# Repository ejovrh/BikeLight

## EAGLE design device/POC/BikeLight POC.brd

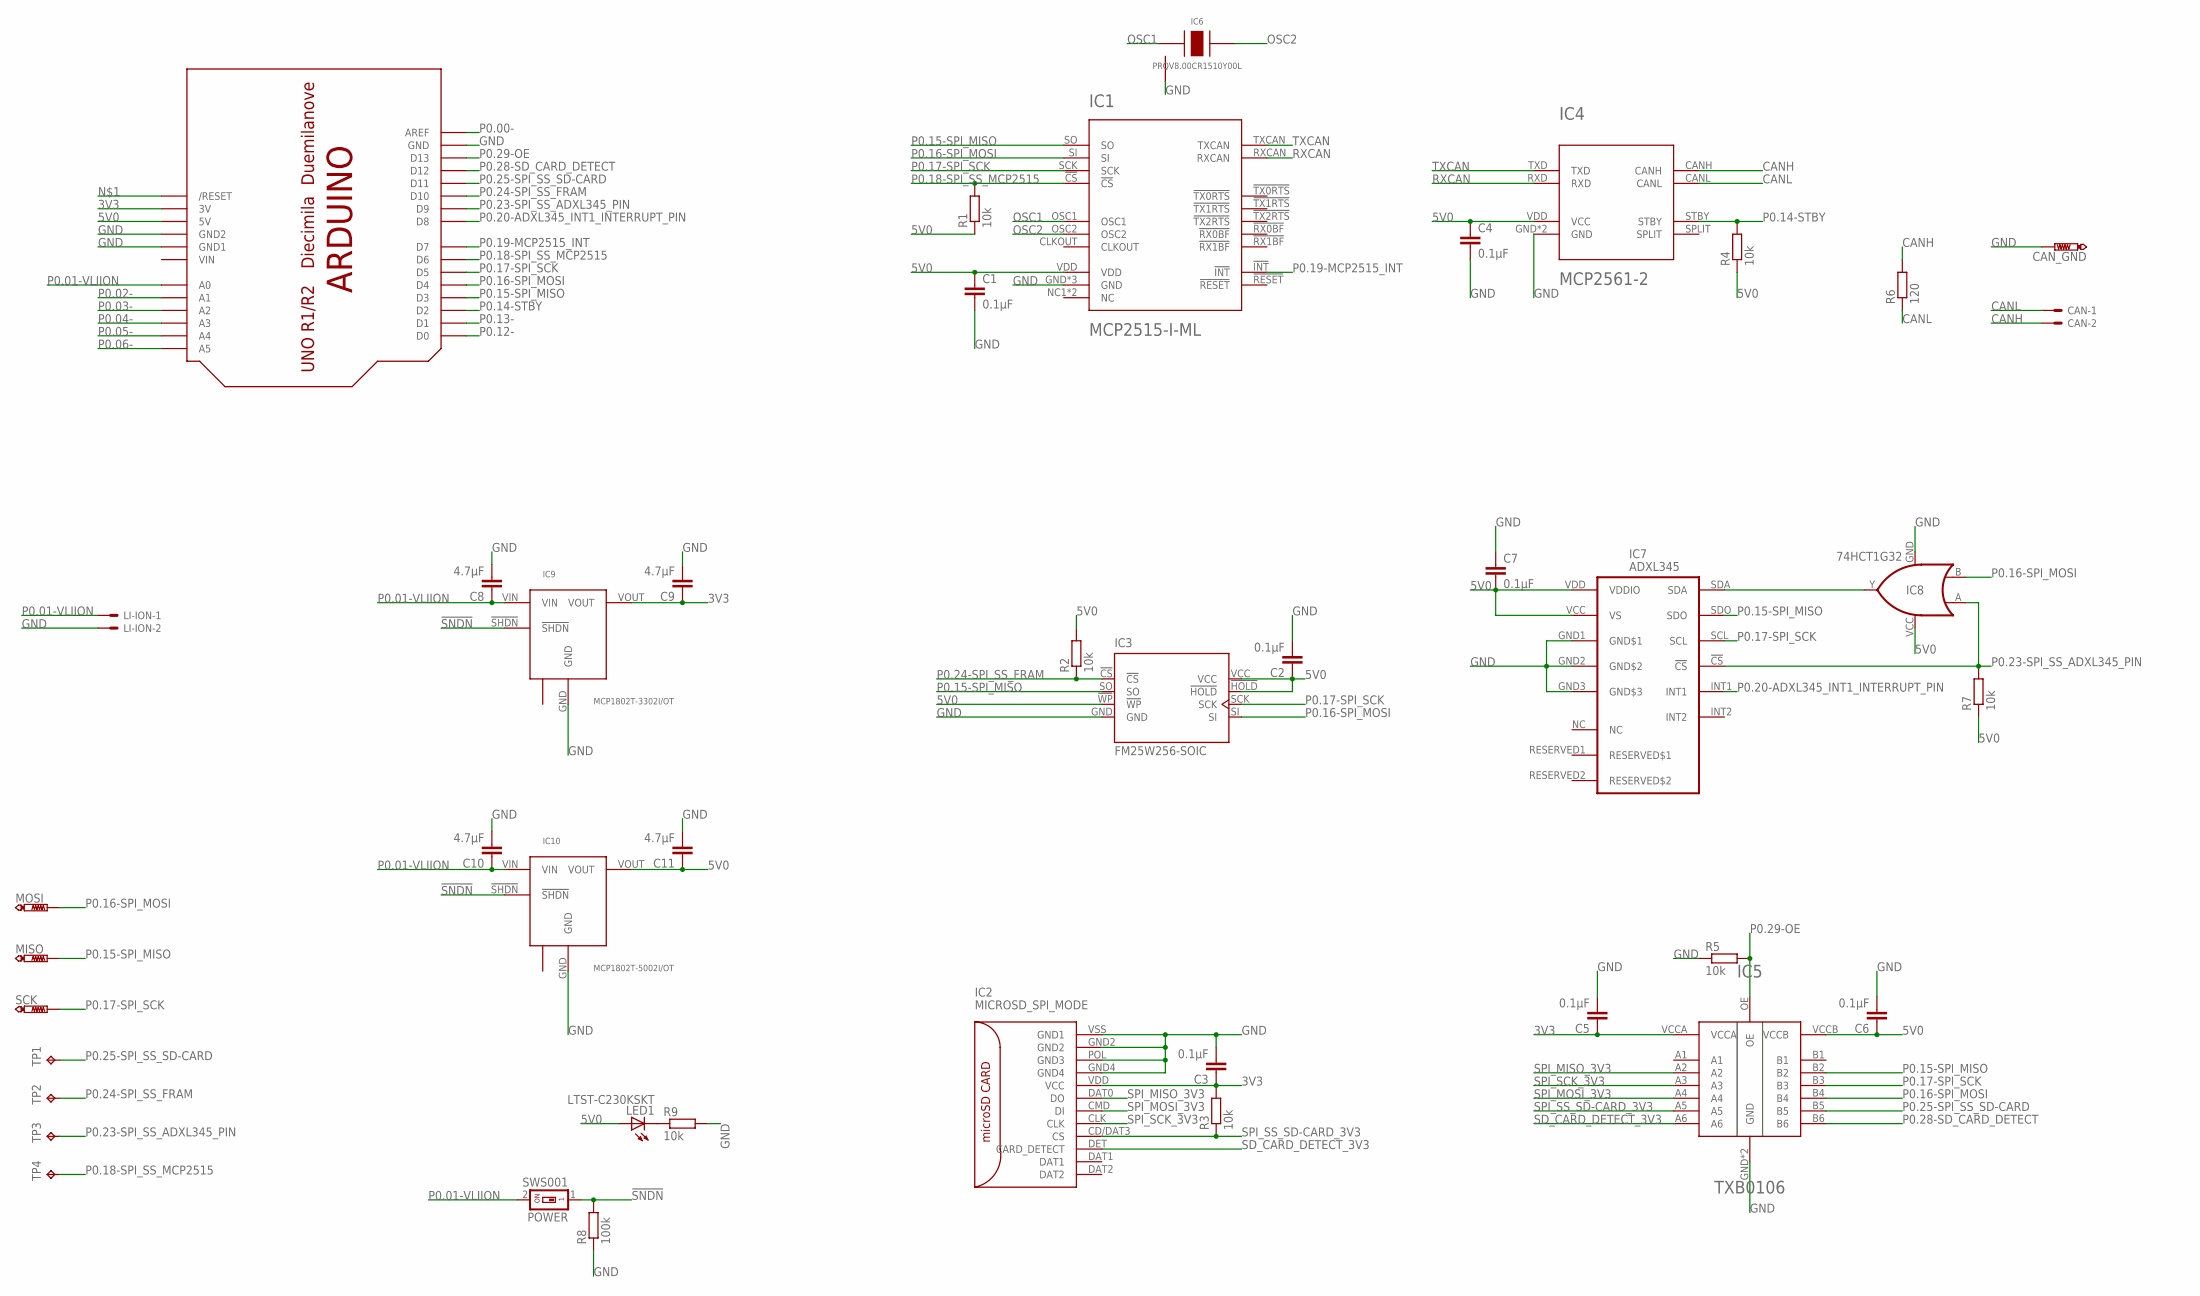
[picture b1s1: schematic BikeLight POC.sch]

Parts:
BRD1: BikeLight POC; ARDUINO
C1, C2, C3, C4, C5, C6, C7: 0.1μF; C0805
C8, C9, C10, C11: 4.7μF; C0805
CAN: 22-23-2021
CAN_GND: PTR1PAD1-13Y; P1-13Y
IC1: MCP2515-I-ML; QFN20
IC2: MICROSD_SPI_MODE; MICRO_SD_CONNECTOR
IC3: FM25W256-SOIC; SOIC08
IC4: MCP2561-2; DFN10
IC5: TXB0106; VQFN16
IC6: PRQV8.00CR1510Y00L; SMT
IC7: ADXL345; LGA14
IC8: 74HCT1G32; SOT353/5
IC9: MCP1802T-3302I/OT; SOT23-5
IC10: MCP1802T-5002I/OT; SOT23-5
LED1: LTST-C230KSKT; CHIPLED_1206
LI-ION: 22-23-2021
MISO: PTR1PAD1-13Y; P1-13Y
MOSI: PTR1PAD1-13Y; P1-13Y
POWER: SWS001; SMS-001
R1, R2, R3, R4, R5, R7, R9: 10k; R0805
R6: 120; R0805
R8: 100k; R0805
SCK: PTR1PAD1-13Y; P1-13Y
TP1, TP2, TP3, TP4: TPPAD1-13; P1-13

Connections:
3V3: BRD1.3V, C3.1, C5.1, C9.1, IC2.VDD (VCC), IC5.VCCA, IC9.VOUT, R3.2
5V0: BRD1.5V, C1.1, C2.1, C4.1, C6.1, C7.2, C11.1, IC1.VDD, IC3.!HOLD!, IC3.!WP!, IC3.VCC, IC4.VDD (VCC), IC5.VCCB, IC7.VCC (VS), IC7.VDD (VDDIO), IC8.VCC, IC10.VOUT, LED1.A, R1.1, R2.2, R4.1, R7.1
!SNDN!: IC9.!SHDN!, IC10.!SHDN!, POWER.1, R8.2
CANH: CAN.2, IC4.CANH, R6.2
CANL: CAN.1, IC4.CANL, R6.1
GND: BRD1.GND, BRD1.GND1, BRD1.GND2, C1.2, C2.2, C3.2, C4.2, C5.2, C6.2, C7.1, C8.2, C9.2, C10.2, C11.2, CAN_GND.TP, IC1.GND, IC1.GND1 (GND), IC1.GND6 (GND), IC2.GND2, IC2.GND4, IC2.POL (GND3), IC2.VSS (GND1), IC3.GND, IC4.GND, IC4.VSS (GND), IC5.GND, IC5.GND1 (GND), IC6.GND, IC7.GND1 (GND$1), IC7.GND2 (GND$2), IC7.GND3 (GND$3), IC8.GND, IC9.GND, IC10.GND, LI-ION.2, R5.1, R8.1, R9.2
unnamed: LED1.C, R9.1
OSC1: IC1.OSC1, IC6.XTAL1
OSC2: IC1.OSC2, IC6.XTAL2
P0.00-: BRD1.AREF
P0.01-VLIION: BRD1.A0, C8.1, C10.1, IC9.VIN, IC10.VIN, LI-ION.1, POWER.2
P0.02-: BRD1.A1
P0.03-: BRD1.A2
P0.04-: BRD1.A3
P0.05-: BRD1.A4
P0.06-: BRD1.A5
P0.12-: BRD1.D0
P0.13-: BRD1.D1
P0.14-STBY: BRD1.D2, IC4.STBY, R4.2
P0.15-SPI_MISO: BRD1.D3, IC1.SO, IC3.SO, IC5.B2, IC7.SDO, MISO.TP
P0.16-SPI_MOSI: BRD1.D4, IC1.SI, IC3.SI, IC5.B4, IC8.B, MOSI.TP
P0.17-SPI_SCK: BRD1.D5, IC1.SCK, IC3.SCK, IC5.B3, IC7.SCL, SCK.TP
P0.18-SPI_SS_MCP2515: BRD1.D6, IC1.!CS!, R1.2, TP4.TP
P0.19-MCP2515_INT: BRD1.D7, IC1.!INT!
P0.20-ADXL345_INT1_INTERRUPT_PIN: BRD1.D8, IC7.INT1
P0.23-SPI_SS_ADXL345_PIN: BRD1.D9, IC7.!CS!, IC8.A, R7.2, TP3.TP
P0.24-SPI_SS_FRAM: BRD1.D10, IC3.!CS!, R2.1, TP2.TP
P0.25-SPI_SS_SD-CARD: BRD1.D11, IC5.B5, TP1.TP
P0.28-SD_CARD_DETECT: BRD1.D12, IC5.B6
P0.29-OE: BRD1.D13, IC5.OE, R5.2
RXCAN: IC1.RXCAN, IC4.RXD
SDA: IC7.SDA, IC8.Y
SD_CARD_DETECT_3V3: IC2.DET (CARD_DETECT), IC5.A6
SPI_MISO_3V3: IC2.DAT0 (DO), IC5.A2
SPI_MOSI_3V3: IC2.CMD (DI), IC5.A4
SPI_SCK_3V3: IC2.CLK, IC5.A3
SPI_SS_SD-CARD_3V3: IC2.CD/DAT3 (CS), IC5.A5, R3.1
TXCAN: IC1.TXCAN, IC4.TXD
VIN: BRD1.VIN

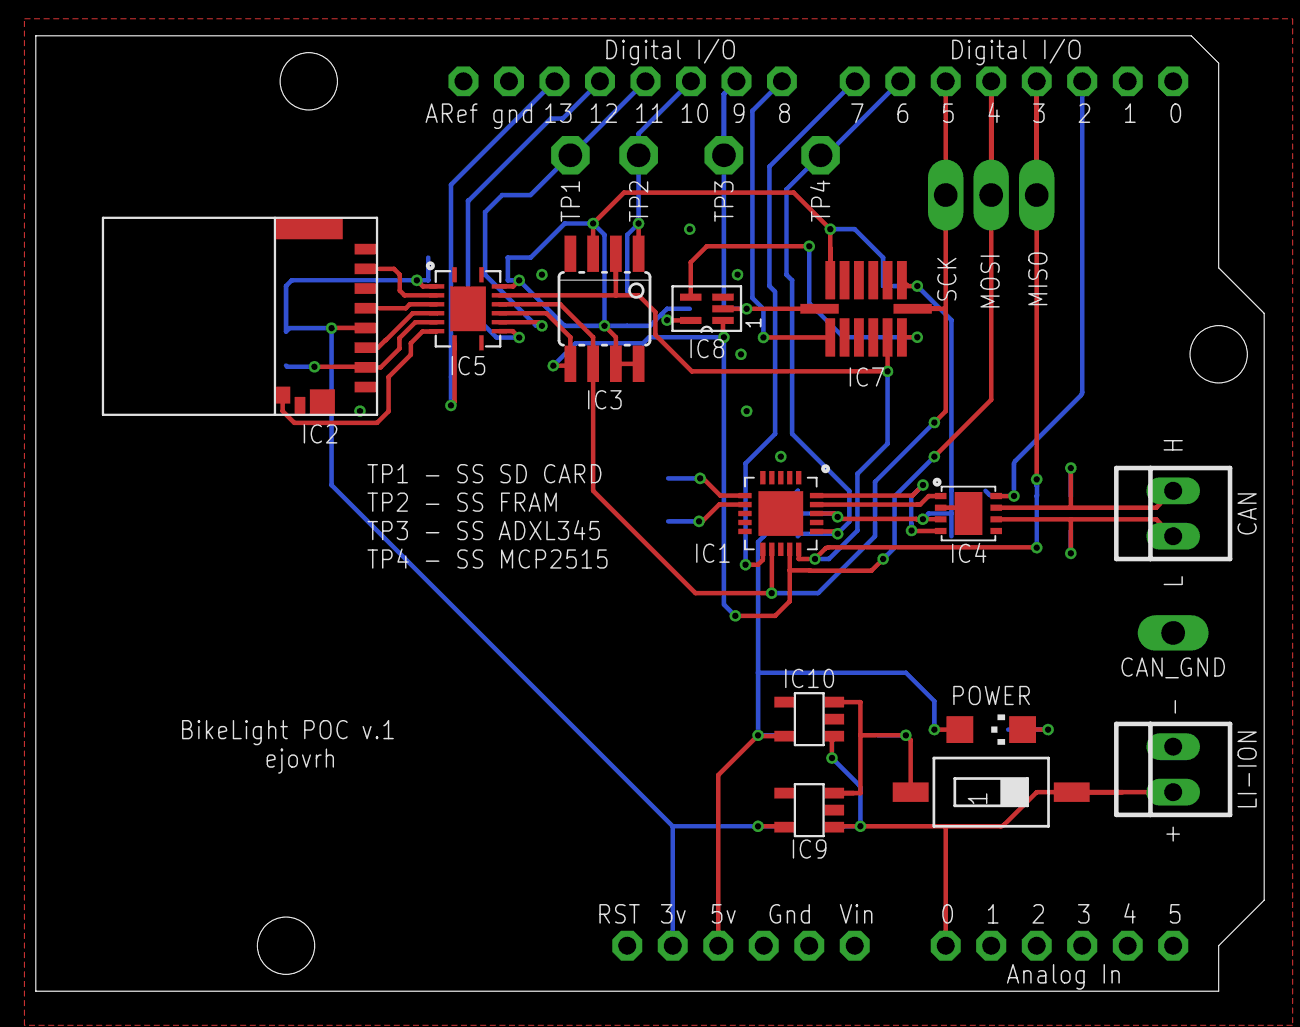
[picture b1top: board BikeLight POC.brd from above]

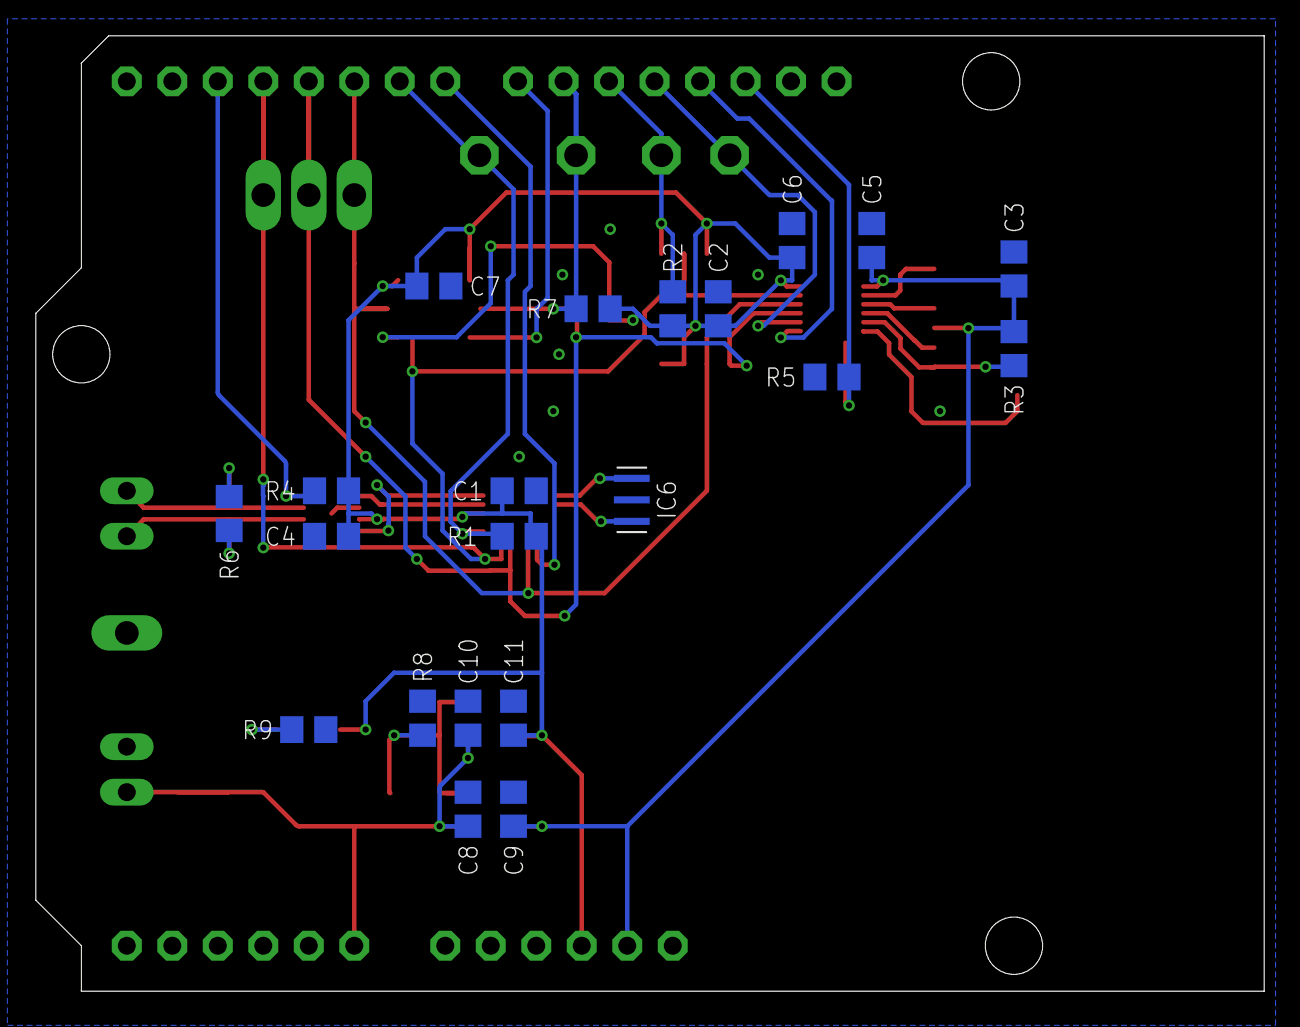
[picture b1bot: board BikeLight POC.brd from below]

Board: 2 copper layers, 68.6 x 53.3 mm, 43 parts (21 on the bottom side), 30 nets.

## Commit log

2017-10-07 - empty arduino uno compatible PCB
2017-10-08 - added empty keil project
2017-10-08 - added SD card with level shifter, FRAM module
2017-10-08 - added TXB0106 - Logic Level Translator datasheet and library
2017-10-08 - added few passives to SD card, FRAM, logic level shifter, can hardware
2017-10-10 - added 8mhz oscillator to mcp2515
2017-12-24 - added eagle.epf
2017-12-28 - named arduino-uno compatible pins P0.XX - added ADXL345
2017-12-30 - added MCP1802 LDO.lbr and datasheet - incorporated LDOs (3V3 and 5V0) into schematic - redeployed brd from scratch
2017-12-31 - finished schematic, ERC is checked and reports only known approved issues
2018-01-01 - finshed layout - added LED to indicate power-on status - remapped most pins to better fit board layout - ERC/DRC report no errors
2018-01-01 - finished layout (silk top and bottom) - created gerbers
2018-01-01 - decided to power the power indicator LED from 5V0 instead from the battery directly
2019-01-02 - recreated epf - eagle project identifier file
